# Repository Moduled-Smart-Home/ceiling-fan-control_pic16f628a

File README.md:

# ceiling-fan-control_pic16f628a

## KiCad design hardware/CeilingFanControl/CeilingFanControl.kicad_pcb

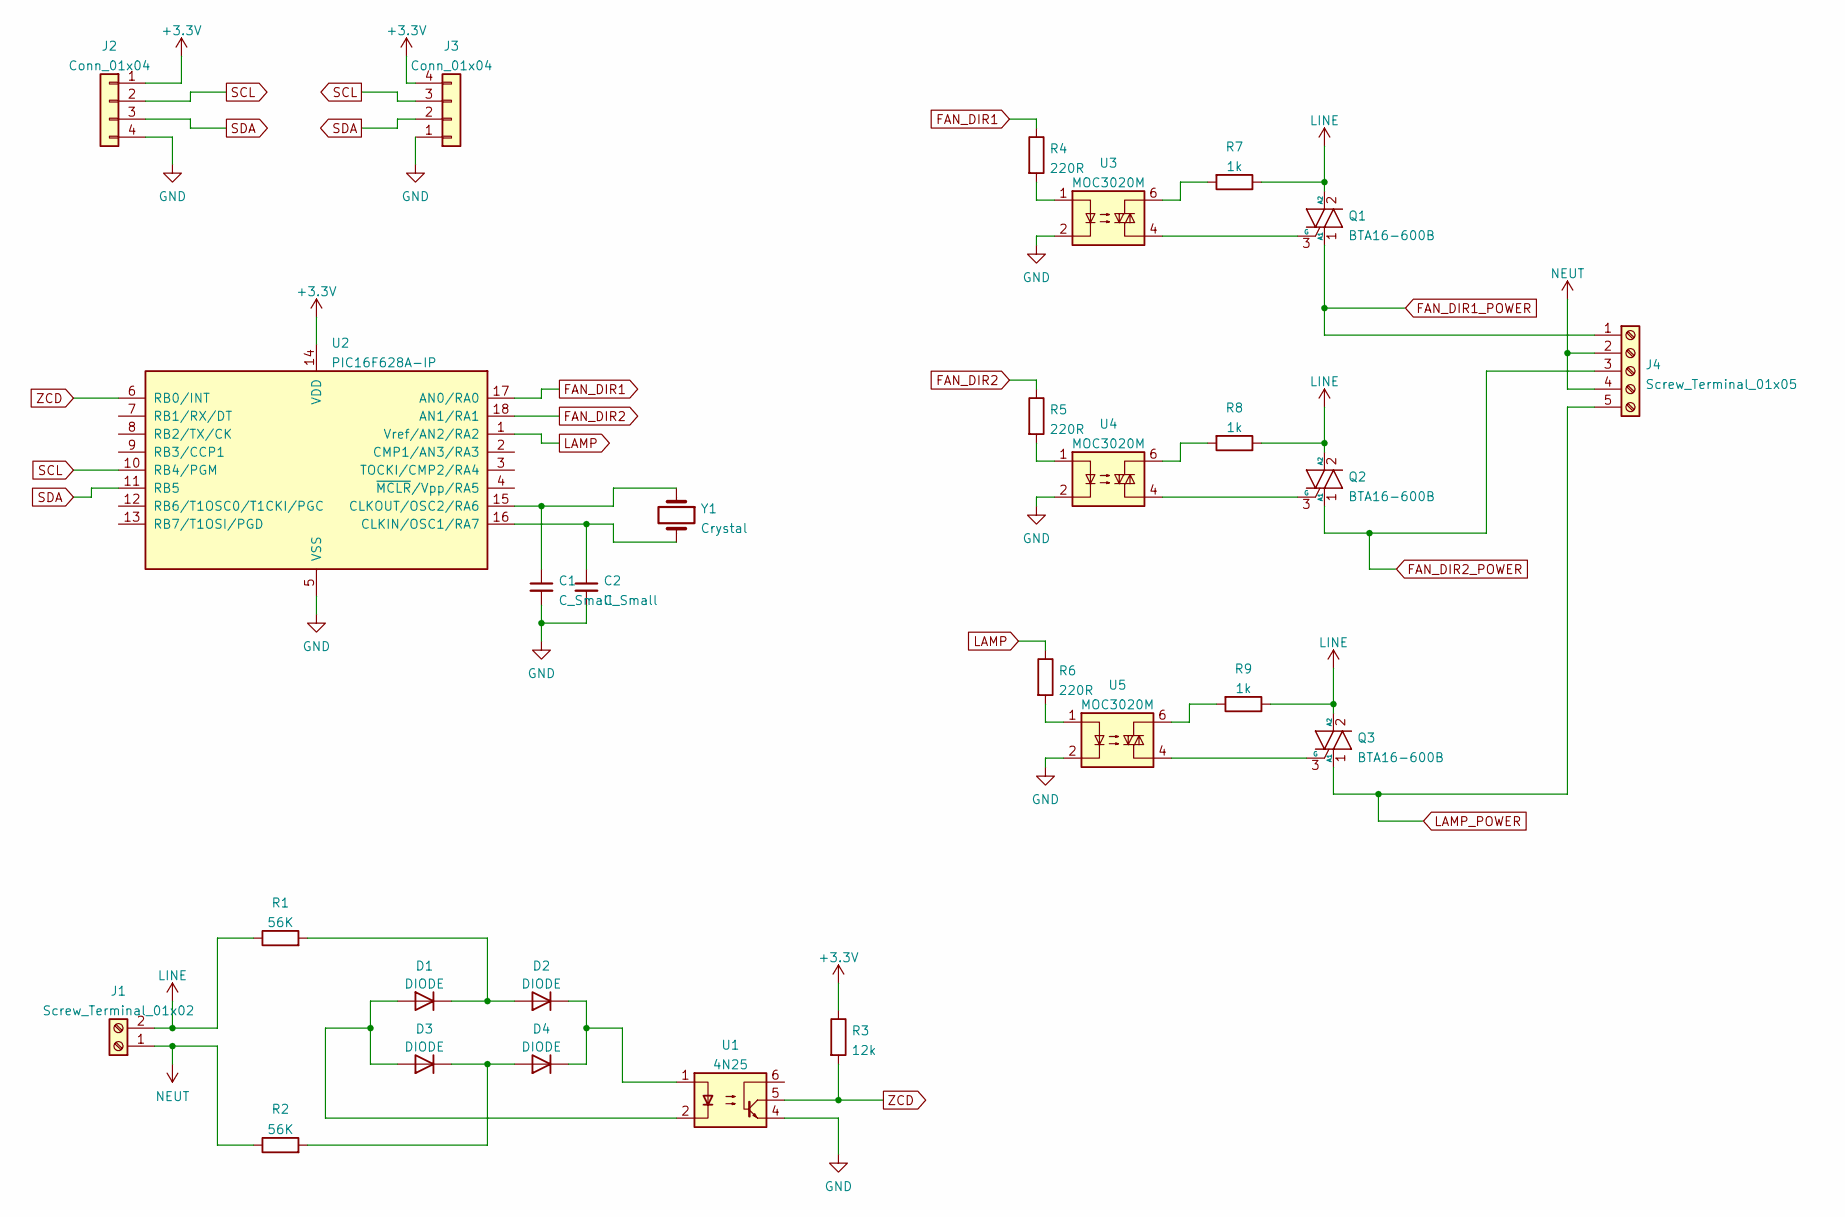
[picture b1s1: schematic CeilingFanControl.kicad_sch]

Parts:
C1, C2: C_Small; C_Disc_D3.0mm_W1.6mm_P2.50mm
D1, D2, D3, D4: DIODE; D_A-405_P7.62mm_Horizontal
J1: Screw_Terminal_01x02; Connector_Spring_Terminal_Block_5.00mm_2P_KF142V
J2, J3: Conn_01x04; JST_EH_S4B-EH_1x04_P2.50mm_Horizontal
J4: Screw_Terminal_01x05; Connector_Spring_Terminal_Block_5.00mm_5P_KF142V
Q1, Q2, Q3: BTA16-600B; TO-220-3_Vertical
R1, R2: 56K; R_Axial_DIN0207_L6.3mm_D2.5mm_P10.16mm_Horizontal
R3: 12k; R_Axial_DIN0207_L6.3mm_D2.5mm_P10.16mm_Horizontal
R4, R5, R6: 220R; R_Axial_DIN0207_L6.3mm_D2.5mm_P10.16mm_Horizontal
R7, R8, R9: 1k; R_Axial_DIN0207_L6.3mm_D2.5mm_P10.16mm_Horizontal
U1: 4N25; DIP-6_W7.62mm
U2: PIC16F628A-IP; DIP-18_W7.62mm
U3, U4, U5: MOC3020M; DIP-6_W7.62mm
Y1: Crystal; Crystal_HC18-U_Vertical

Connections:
+3V3: J2.1, J3.4, R3.1, U2.14 (VDD)
FAN_DIR1: R4.1, U2.17 (AN0/RA0)
FAN_DIR1_POWER: J4.1, Q1.1 (A1)
FAN_DIR2: R5.1, U2.18 (AN1/RA1)
FAN_DIR2_POWER: J4.3, Q2.1 (A1)
GND: C1.2, C2.2, J2.4, J3.1, U1.4, U2.5 (VSS), U3.2, U4.2, U5.2
LAMP: R6.1, U2.1 (Vref/AN2/RA2)
LAMP_POWER: J4.5, Q3.1 (A1)
LINE: J1.2, Q1.2 (A2), Q2.2 (A2), Q3.2 (A2), R1.1, R7.1, R8.1, R9.1
NEUT: J1.1, J4.2, J4.4, R2.1
unnamed: C1.1, U2.15 (CLKOUT/OSC2/RA6), Y1.1
unnamed: C2.1, U2.16 (CLKIN/OSC1/RA7), Y1.2
unnamed: D1.1 (K), D2.2 (A), R1.2
unnamed: D1.2 (A), D3.2 (A), U1.2
unnamed: D2.1 (K), D4.1 (K), U1.1
unnamed: D3.1 (K), D4.2 (A), R2.2
unnamed: Q1.3 (G), U3.4
unnamed: Q2.3 (G), U4.4
unnamed: Q3.3 (G), U5.4
unnamed: R4.2, U3.1
unnamed: R5.2, U4.1
unnamed: R6.2, U5.1
unnamed: R7.2, U3.6
unnamed: R8.2, U4.6
unnamed: R9.2, U5.6
SCL: J2.2, J3.3, U2.10 (RB4/PGM)
SDA: J2.3, J3.2, U2.11 (RB5)
ZCD: R3.2, U1.5, U2.6 (RB0/INT)

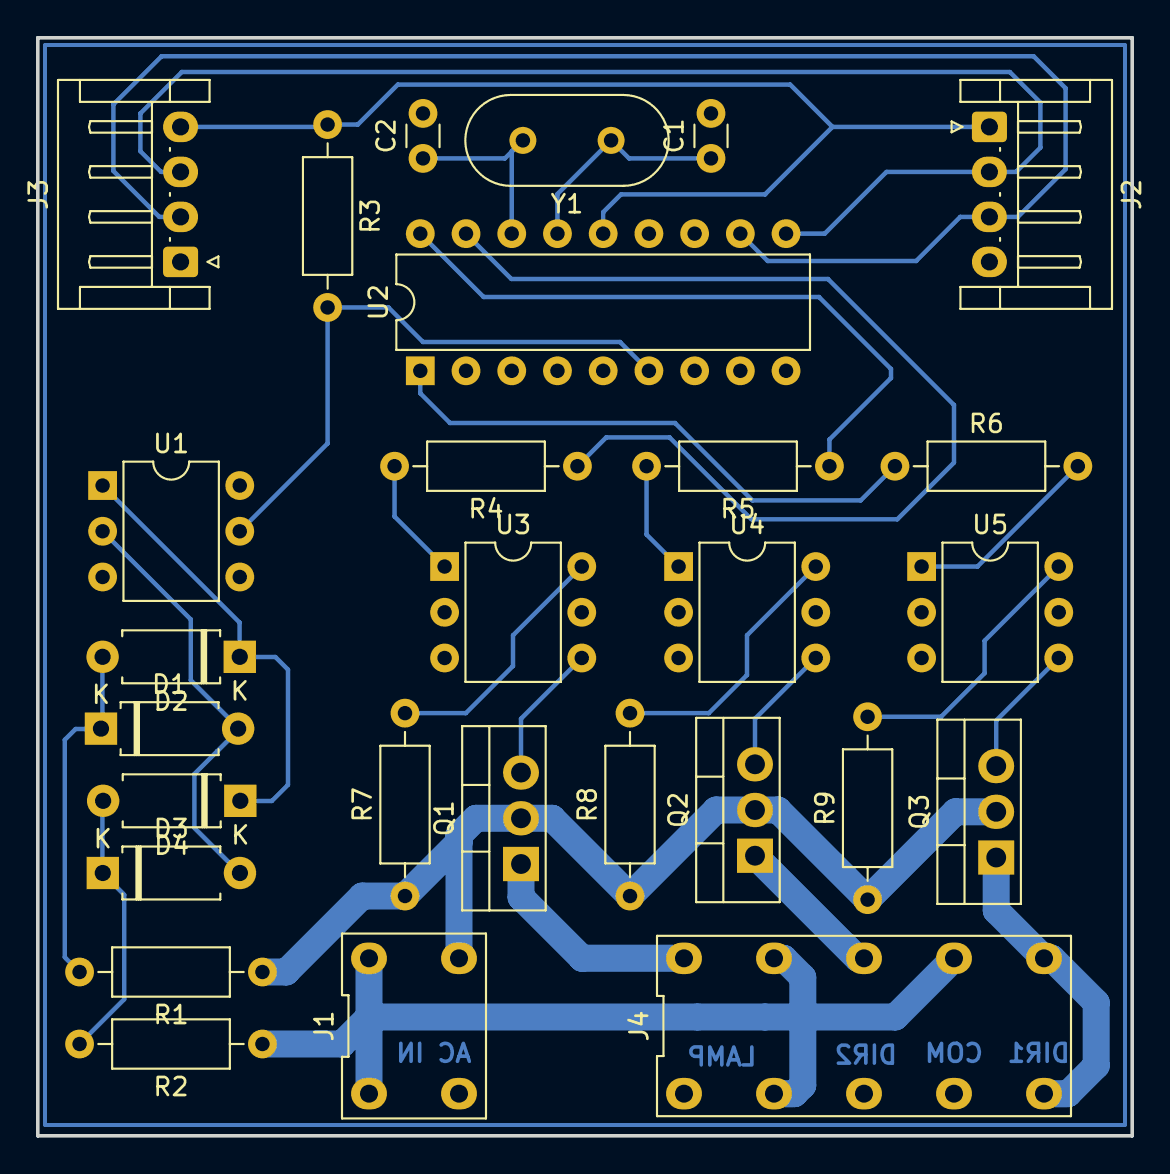
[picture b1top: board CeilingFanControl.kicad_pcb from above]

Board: 2 copper layers, 60.8 x 61.0 mm, 28 parts (0 on the bottom side), 28 nets.

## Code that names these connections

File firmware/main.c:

/*
 * File:   newmain.c
 * Author: conrado
 *
 * Created on December 12, 2021, 12:20 AM
 */

// PIC16F628A Configuration Bit Settings

// 'C' source line config statements

// CONFIG
#pragma config FOSC = HS    // Oscillator Selection bits (HS oscillator: High-speed crystal/resonator on RA6/OSC2/CLKOUT and RA7/OSC1/CLKIN)
#pragma config WDTE = OFF       // Watchdog Timer Enable bit (WDT disabled)
#pragma config PWRTE = ON       // Power-up Timer Enable bit (PWRT enabled)
#pragma config MCLRE = OFF      // RA5/MCLR/VPP Pin Function Select bit (RA5/MCLR/VPP pin function is digital input, MCLR internally tied to VDD)
#pragma config BOREN = OFF      // Brown-out Detect Enable bit (BOD disabled)
#pragma config LVP = OFF         // Low-Voltage Programming Enable bit (RB4/PGM pin has PGM function, low-voltage programming enabled)
#pragma config CPD = OFF        // Data EE Memory Code Protection bit (Data memory code protection off)
#pragma config CP = OFF         // Flash Program Memory Code Protection bit (Code protection off)

// #pragma config statements should precede project file includes.
// Use project enums instead of #define for ON and OFF.

#include <xc.h> 
#define _XTAL_FREQ 20000000

#include "i2c.h"

PORTAbits_t LATCHA;
PORTBbits_t LATCHB, LATCHB_prev;

#define LED LATCHA.RA3
#define FAN_DIR1 LATCHA.RA0
#define FAN_DIR2 LATCHA.RA1
#define LAMP LATCHA.RA2

//#define TIME_TRIGG_us 6500
#define TIME_HOLD_us 1000
#define TIME_TRIGG_MAX_us 7333
#define TIME_TRIGG_MIN_us 0

#define TIME_TRIGG_POT1_us 6500
#define TIME_TRIGG_POT2_us 4000
#define TIME_HOLD_us 1000

static unsigned short TICKS_PER_US = _XTAL_FREQ / (4 * 1000000);
static unsigned short TIMER_SETUP_POT, TIMER_SETUP_POT1, TIMER_SETUP_POT2, TIMER_SETUP_HOLD;

typedef enum {ZERO_CROSSED, TRIGGED, READY} triac_state_t;
triac_state_t triac_fan;
triac_state_t triac_lamp;

typedef enum {OFF, ON_DIR1, ON_DIR2} fan_state_t;
fan_state_t fan_state;

void toggleLED(void) {
    LED = !LED;
    PORTAbits = LATCHA;
}

void setLED(unsigned char value) {
    LED = value;
    PORTAbits = LATCHA;
}

void setLAMP(unsigned char value) {
    LAMP = value;
    PORTAbits = LATCHA;
}

void setFanDir1(unsigned char value) {
    FAN_DIR2 = 0;
    FAN_DIR1 = value;
    PORTAbits = LATCHA;
}

void setFanDir2(unsigned char value) {
    FAN_DIR1 = 0;
    FAN_DIR2 = value;
    PORTAbits = LATCHA;
}

void  __interrupt(high_priority) myHighIsr(void) {
    if (RBIE && RBIF) {
        INTE = 0;
        TMR1IE = 0;
        LATCHB = PORTBbits;
        i2cInterruptHandle(LATCHB.RB4, LATCHB.RB5);
        RBIF=0;
        INTE = 1;
        TMR1IE = 1;
    }
    
    if (INTE && INTF) {
        INTF=0;
        
        if (fan_state != OFF) {
            TMR1 = TIMER_SETUP_POT;
            triac_fan = ZERO_CROSSED;
            TMR1IE = 1; //enable TMR1 interrupt
            TMR1ON = 1; //start TMR1
        }        
    }
    
    if (TMR1IE && TMR1IF) {
        TMR1IF = 0;
        
        if (triac_fan == ZERO_CROSSED) {
            switch (fan_state) {
                case ON_DIR1:
                    setFanDir1(1);
                    break;
                    
                case ON_DIR2:
                    setFanDir2(1);
                    break;
            }

            TMR1 = TIMER_SETUP_HOLD;
            triac_fan = TRIGGED;
        }
        
        else if (triac_fan == TRIGGED) {
            setFanDir1(0);
            setFanDir2(0);
            triac_fan = READY;
            TMR1IE = 0; //disable TMR1 interrupt
            TMR1ON = 0; //stop TMR1
        }
    }
}


void main(void) {
    TIMER_SETUP_POT = 65535 - 0.9*TIME_TRIGG_MAX_us*TICKS_PER_US; // start with minimum power
    TIMER_SETUP_HOLD = 65535 - (TIME_HOLD_us * TICKS_PER_US);
    
     // XTAL Oscilator
    TRISAbits.TRISA6 = 1;
    TRISAbits.TRISA7 = 1;
    
    // Configuration LED e MOC
    PCONbits.OSCF=1;
    TRISAbits.TRISA3 = 0; //Output - LED
    TRISAbits.TRISA0 = 0; //Output - FAN_DIR1
    TRISAbits.TRISA1 = 0; //Output - FAN_DIR2
    TRISAbits.TRISA2 = 0; //Output - LAMP
    
    // Configuration Zero Crossing Interrupt
    TRISBbits.TRISB0 = 1;
    INTCONbits.GIE=1;
    INTCONbits.INTE=1;
    OPTION_REGbits.INTEDG=1;
    
    LATCHA = PORTAbits; // Initialize Latch with actual port values
    
    //TIMER1 config
    TMR1ON = 0; //ensure tmr1 is stopped
    TMR1CS = 0; //timer mode
    PEIE = 1; //enable peripheral interrupt
    
    T1CKPS0 = 0; //prescale 1:1
    T1CKPS1 = 0;
    
    setSlaveAddress8bits(0xAA);
    
    DATA_RECEIVED = 0;
    
    fan_state = OFF;
    triac_fan = READY;
    
    int ret;
    ret = startI2C();
    
    setLED(0);
    
    setLAMP(1); 
    
    while(1) {      

//        if (i2c_state == REC_DATA) {
//            toggleLED();
//        }
        
        if (DATA_RECEIVED == 1) {

            switch (cmd) {
                case LED_OFF:
                   setLED(0);
                   break;
                
                case LED_ON:
                    setLED(1);
                    break;
                    
                case FAN_OFF:
                    fan_state = OFF;
                    break;
                    
                case FAN_ON_DIR1:
                    fan_state = ON_DIR1;
                    break;
                    
                case FAN_ON_DIR2:
                    fan_state = ON_DIR2;
                    break;
                        
                case POT1:
                    TIMER_SETUP_POT = 65535 - 0.95*TIME_TRIGG_MAX_us*TICKS_PER_US;
                    break;
                    
                case POT2:
                    TIMER_SETUP_POT = 65535 - 0.90*TIME_TRIGG_MAX_us*TICKS_PER_US;
                    break;
                
                case POT3:
                    TIMER_SETUP_POT = 65535 - 0.85*TIME_TRIGG_MAX_us*TICKS_PER_US;
                    break;
                
                case POT4:
                    TIMER_SETUP_POT = 65535 - 0.65*TIME_TRIGG_MAX_us*TICKS_PER_US;
                    break;
                    
                case POT5:
                    TIMER_SETUP_POT = 65535 - 0.30*TIME_TRIGG_MAX_us*TICKS_PER_US;
                    break;
                    
                case LAMP_ON:
                    setLAMP(1);
                    break;
                    
                case LAMP_OFF:
                    setLAMP(0);
                    break;
            }
            
            DATA_RECEIVED = 0;
        }
    }
    
    return;
}

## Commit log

2022-01-29 Uploading initial testing code
2022-01-30 Implementa teste 1 canal de controle 2 níveis de potência
2022-01-31 Melhora forma de calculo de setup de TIMER1
2022-02-01 Adiciona mais comandos de teste
2022-02-01 Adicona mais niveis de potencia
2022-02-08 Ajusta tempos de disparo
2022-02-08 Primeira versão da placa
2022-02-13 Adiciona controle do canal de lampada
2022-02-13 PCI com e sem zonas de GND
2022-09-23 Initialçizing with LAMP on
2023-03-05 Commit befora creating tag
2024-12-15 commit before system update
